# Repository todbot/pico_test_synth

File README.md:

# pico_test_synth

A simple 
[Raspberry Pi Pico RP2040 or Pico 2 RP2350](https://www.raspberrypi.com/documentation/microcontrollers/raspberry-pi-pico.html)-based
synth to experiment with [`synthio`](https://github.com/todbot/circuitpython-synthio-tricks) and [Mozzi](https://github.com/sensorium/Mozzi).

### pico_test_synth2

### pico_test_synth, the original

<h3>video demo</h3>

** **[Available on Tindie](https://www.tindie.com/products/todbot/pico_test_synth/)** **

### Features

* [PCM5102 I2S DAC](https://todbot.com/blog/2023/05/16/cheap-stereo-line-out-i2s-dac-for-circuitpython-arduino-synths/) footprint for high-quality stereo audio out
* Optoisolated MIDI Input via [MIDI TRS-A 3.5mm jack](https://www.perfectcircuit.com/make-noise-0-coast-midi-cable.html)
* MIDI output via MIDI TRS-A 3.5mm jack
* Two pots for controlling parameters
* One switch for controlling parameters
* 16 capsense touch buttons for synth triggering
* USB MIDI in/out of course too
* **(NOTE: the pico_test_synth1 PCB will NOT work with the Pico2, since its RP2350 chip has a hardware error)**

#### pico_test_synth2 vs pico_test_synth

- Both use the same components
- Both run the same code 
- Both fit in the same enclosure
- `pico_test_synth2` drawn in Kicad; `pico_test_synth` drawn in Eagle
- `pico_test_synth2` has square buttons; `pico_test_synth` has round buttons
- `pico_test_synth2` can work with Pico 2 and Pico 
- `pico_test_synth` can only work with Pico1

### Software

Programs written for [`qtpy_synth`](https://github.com/todbot/qtpy_synth/)
will work with this board too with minimal changes.

Some programs written specifically for this board:

* [TBish](https://github.com/todbot/pico_test_synth/tree/main/circuitpython/tbish/) - a TB303-like synth demo ([video demo](https://www.youtube.com/watch?v=1AflpXbEIno))
* [monosynth1](https://github.com/todbot/pico_test_synth/tree/main/arduino/monosynth1) - a full Moog-like monosynth written in Arduino & Mozzi 
* [hwtest](https://github.com/todbot/pico_test_synth/tree/main/circuitpython/hwtest/code.py) - test out the hardware with a simple synth ([video demo](https://www.youtube.com/watch?v=9U2Dn7ckdbs))
* [wavesynth](https://github.com/todbot/pico_test_synth/tree/main/circuitpython/wavesynth/) - port of wavesynth for qtpy_synth board with some improvements

#### See also:
- [CircuitPython Synthio Tricks](https://github.com/todbot/circuitpython-synthio-tricks)
  - Contains [many other synthio examples](https://github.com/todbot/circuitpython-synthio-tricks/tree/main/examples) that can work with this synth with minimal changes
- [Synthio Tutorial](https://todbot.github.io/CircuitPython_Synthio_Tutorial/) 
  - a getting-started guide for `synthio` ending with some full synthesiser voices 

### Enclosure

As seen in the photos, there is a simple [3d-printable enclosure available on Printables](https://www.printables.com/model/784414-case-for-pico_test_synth-circuitpython-synthesizer). 
It's fast to print and you can snap the PCB in to quickly get started,
or use M2.5 screws and nuts to secure the PCB more permanently.

### Pins used

The board uses all of the Raspberry Pi Pico pins:

* `board.GP28` - middle button
* `board.GP27` - right knob
* `board.GP26` - left knob
* `board.GP22` - I2S data
* `board.GP21` - I2S LR  clock
* `board.GP20` - I2S bit clock
* `board.GP19` - I2C SCL for OLED display
* `board.GP18` - I2C SDA for OLED display
* `board.GP17` - TRS UART MIDI in
* `board.GP16` - TRS UART MIDI out
* `board.GP15`..`board.GP0` -- touch pads 1-16

For more details see [`hwtest/code.py`](https://github.com/todbot/pico_test_synth/tree/main/circuitpython/hwtest/code.py).

### Schematics

#### pico_test_synth2 ####

#### pico_test_synth, original ####

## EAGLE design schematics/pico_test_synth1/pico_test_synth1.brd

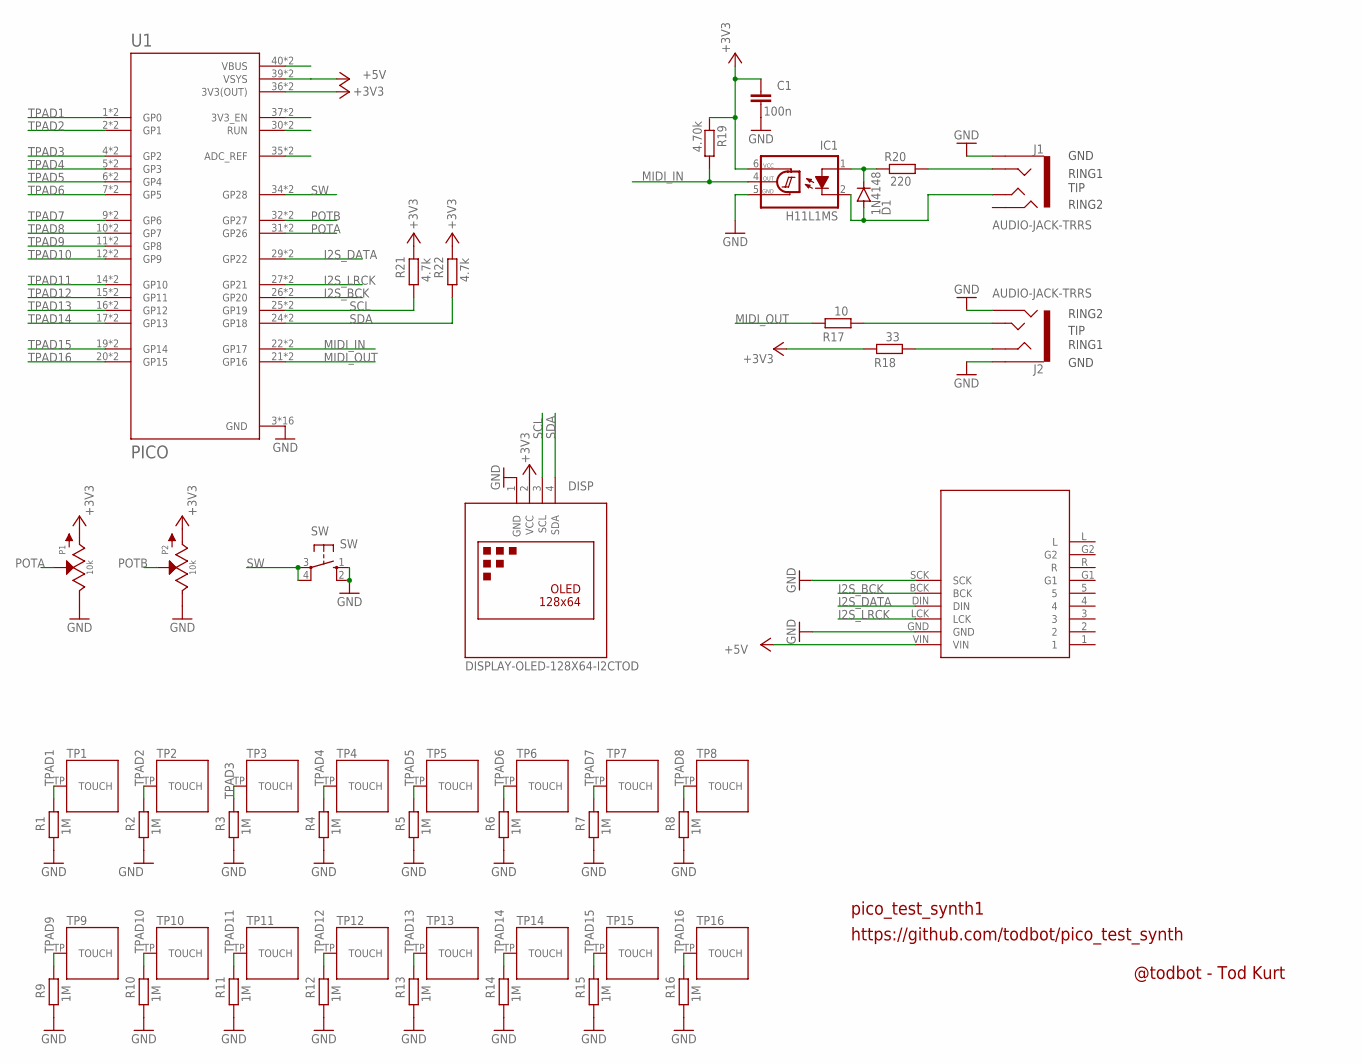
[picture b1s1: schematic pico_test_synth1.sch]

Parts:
C1: 100n; C0805
D1: 1N4148; SOD123
DISP: DISPLAY-OLED-128X64-I2CTOD; DISPLAY-OLED-128X64-I2C-TOD
IC1: H11L1MS; DIL6-SMD; MPN2 H11L1S; LCSC C78589
J1: AUDIO-JACK-TRRS; PJ-320D_SPARKFUN
J2: AUDIO-JACK-TRRS; PJ-320D_SPARKFUN; LCSC C431535
P1, P2: 10k; OG-POTS_ALPS_POT_VERTICAL_WITHBIGKNOB
R1, R2, R3, R4, R5, R6, R7, R8, R9, R10, R11, R12, R13, R14, R15, R16: 1M; R0805
R17: 10; R0805
R18: 33; R0805
R19: 4.70k; R0805
R20: 220; R0805
R21, R22: 4.7k; R0805
SW: SW; B3F-10XX
TP1, TP2, TP3, TP4, TP5, TP6, TP7, TP8, TP9, TP10, TP11, TP12, TP13, TP14, TP15, TP16: TOUCHPADA; TOUCHPADA_0.5IN
U1: PICO; PICO-PKG-NO_DEBUG
U2: I2S_PCM_51XX_SOUNDCARD; I2S_PCM_5100_SOUNDCARD

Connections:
+3V3: C1.1, DISP.2 (VCC), IC1.6 (VCC), P1.P$3 (A), P2.P$3 (A), R18.1, R19.1, R21.1, R22.1, U1.36 (3V3(OUT)), U1.P$36 (3V3(OUT))
+5V: U1.39 (VSYS), U1.P$39 (VSYS), U2.VIN
GND: C1.2, DISP.1 (GND), IC1.5 (GND), J1.EARTH, J2.EARTH, J2.RING2, P1.P$1 (E), P2.P$1 (E), R1.2, R2.2, R3.2, R4.2, R5.2, R6.2, R7.2, R8.2, R9.2, R10.2, R11.2, R12.2, R13.2, R14.2, R15.2, R16.2, SW.1 (S), SW.2 (S1), U1.3 (GND), U1.8 (GND), U1.13 (GND), U1.18 (GND), U1.23 (GND), U1.28 (GND), U1.33 (GND), U1.38 (GND), U1.P$3 (GND), U1.P$8 (GND), U1.P$13 (GND), U1.P$18 (GND), U1.P$23 (GND), U1.P$28 (GND), U1.P$33 (GND), U1.P$38 (GND), U2.GND, U2.SCK
I2S_BCK: U1.26 (GP20), U1.P$26 (GP20), U2.BCK
I2S_DATA: U1.29 (GP22), U1.P$29 (GP22), U2.DIN
I2S_LRCK: U1.27 (GP21), U1.P$27 (GP21), U2.LCK
MIDI_IN: IC1.4 (OUT), R19.2, U1.22 (GP17), U1.P$22 (GP17)
MIDI_OUT: R17.1, U1.21 (GP16), U1.P$21 (GP16)
unnamed: U1.35 (ADC_REF), U1.P$35 (ADC_REF)
unnamed: J1.RING1, R20.2
unnamed: U1.30 (RUN), U1.P$30 (RUN)
unnamed: U1.37 (3V3_EN), U1.P$37 (3V3_EN)
unnamed: U1.40 (VBUS), U1.P$40 (VBUS)
unnamed: D1.C, IC1.1 (A), R20.1
unnamed: D1.A, IC1.2 (C), J1.TIP
unnamed: J2.RING1, R18.2
unnamed: J2.TIP, R17.2
POTA: P1.P$2 (S), U1.31 (GP26), U1.P$31 (GP26)
POTB: P2.P$2 (S), U1.32 (GP27), U1.P$32 (GP27)
SCL: DISP.3 (SCL), R21.2, U1.25 (GP19), U1.P$25 (GP19)
SDA: DISP.4 (SDA), R22.2, U1.24 (GP18), U1.P$24 (GP18)
SW: SW.3, SW.4 (P1), U1.34 (GP28), U1.P$34 (GP28)
TPAD1: R1.1, TP1.TP, U1.1 (GP0), U1.P$1 (GP0)
TPAD2: R2.1, TP2.TP, U1.2 (GP1), U1.P$2 (GP1)
TPAD3: R3.1, TP3.TP, U1.4 (GP2), U1.P$4 (GP2)
TPAD4: R4.1, TP4.TP, U1.5 (GP3), U1.P$5 (GP3)
TPAD5: R5.1, TP5.TP, U1.6 (GP4), U1.P$6 (GP4)
TPAD6: R6.1, TP6.TP, U1.7 (GP5), U1.P$7 (GP5)
TPAD7: R7.1, TP7.TP, U1.9 (GP6), U1.P$9 (GP6)
TPAD8: R8.1, TP8.TP, U1.10 (GP7), U1.P$10 (GP7)
TPAD9: R9.1, TP9.TP, U1.11 (GP8), U1.P$11 (GP8)
TPAD10: R10.1, TP10.TP, U1.12 (GP9), U1.P$12 (GP9)
TPAD11: R11.1, TP11.TP, U1.14 (GP10), U1.P$14 (GP10)
TPAD12: R12.1, TP12.TP, U1.15 (GP11), U1.P$15 (GP11)
TPAD13: R13.1, TP13.TP, U1.16 (GP12), U1.P$16 (GP12)
TPAD14: R14.1, TP14.TP, U1.17 (GP13), U1.P$17 (GP13)
TPAD15: R15.1, TP15.TP, U1.19 (GP14), U1.P$19 (GP14)
TPAD16: R16.1, TP16.TP, U1.20 (GP15), U1.P$20 (GP15)

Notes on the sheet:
pico_test_synth1
https://github.com/todbot/pico_test_synth
RING2
RING1
GND
TIP
@todbot - Tod Kurt

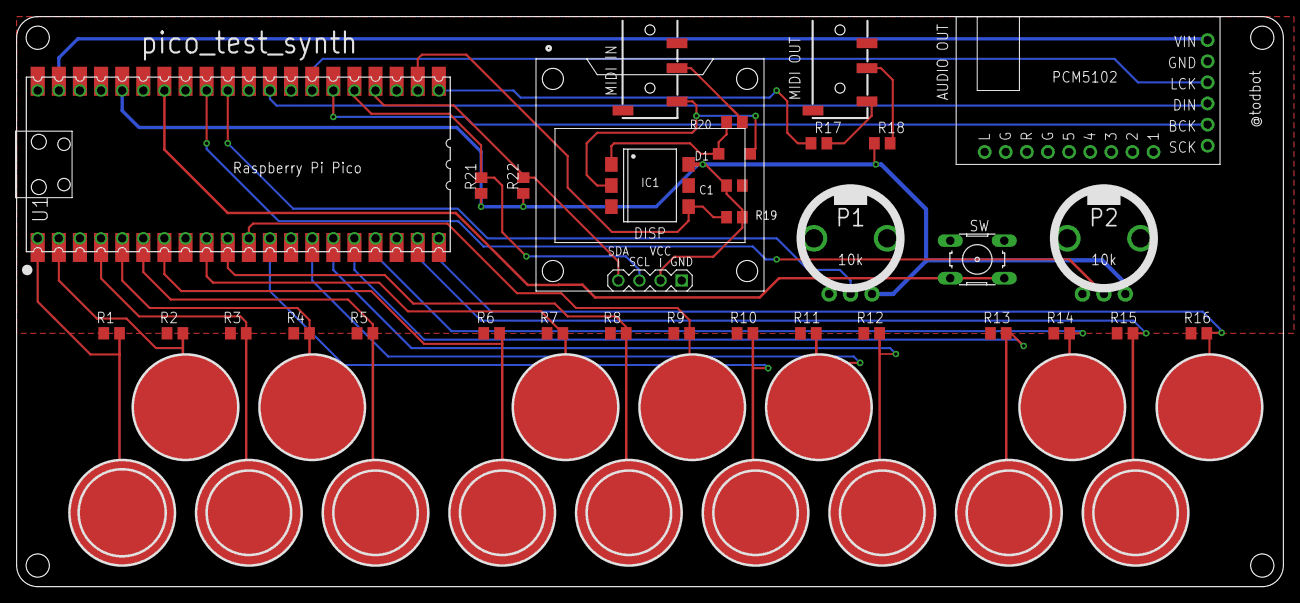
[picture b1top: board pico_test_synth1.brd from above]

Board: 2 copper layers, 152.4 x 68.6 mm, 49 parts (0 on the bottom side), 38 nets.

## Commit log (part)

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2023-08-08 first
2023-08-18 fix up pin usage typos, addresses issue #1
2023-11-22 add synth w/ basic hardware abstraction
2023-11-22 typo fix
2023-11-23 synth1
2024-02-16 clean up hwtest, add rudimentary MIDI receive
2024-02-16 cleanup hwtest a little
2024-02-16 first cut at port of wavesynth from qtpy_synth
2024-02-16 cleanup wavesynth app
2024-02-17 add octave and volume to synthio_instrument patches, expose those params in wavesynth, misc cleanups and fixes. still hate pickup mode
2024-02-17 mention wavesynth in readme
2024-02-17 wavesynth install notes
2024-02-26 finally checking in the restructuring
2024-02-27 add case link to README
2024-02-27 fix wavesynth bugs
2024-02-28 fix more new wavesynth bugs
2024-02-28 wavesynth fixup
2024-02-29 more wavesynth fixes
2024-02-29 wavesynth back to async
2024-03-01 wavesynth filter env works more like it should now
2024-03-01 add some docs
2024-03-02 progress on patch save/load
2024-03-02 wavesynth: patch save/load sorta works, added patch name to display, reworked wave_select logic, added noise wave_select
2024-03-03 wavesynth gauges now redraw on patch selection
2024-03-03 wavesynth twiddling
2024-03-03 wavesynth add splashscreen
2024-03-03 wavesynth instrument.py cleanup
2024-03-03 small hwtest amp env change
2024-03-04 make all waves be half-amplitude (16833) for better multi-voice summing, split out load/save UI actions a little
2024-03-04 wavesynth: add basic velocity sensitivity
2024-03-04 wavesynth: need boot.py to save patches
2024-03-04 fix exec bit on patch_saver.py
2024-03-05 wavesynth: cleanup and added start of demo patch bank
2024-03-28 fix video demo link in readme
2024-07-04 finally getting some arduino examples
2024-07-06 working on arduino gui
2024-07-18 small updates
2024-07-28 add touch keys to monosynth1
2024-07-28 monosynth1: add serial midi in, add start of display
2025-02-15 route +5V to PCM5102 module instead of +3V3, fixes #2
2025-04-15 redraw board in kicad, add ability for using pico2 rp2350
2025-04-16 fixes
2025-04-18 pcb2 cleanup before production
2025-04-18 move pico_test_synth1 sch
2025-04-25 finally check in captouch-only hwtest
2025-04-28 update hwtest for modern circuitpython
2025-05-03 fix up hwtest/code.py a little
2025-05-05 pico_test_synth2 updates
2025-05-15 add pico_test_synth2 to readme
2025-05-15 adj img widths
2025-05-15 add pico_test_synth2 vs original differences
2025-05-25 finally checking in TB-like synth
2025-05-25 finally checked in
2025-05-26 tbish now has touchpad control
2025-05-26 tbish tuning
2025-05-26 tbish slide sorta working
2025-05-27 tbish: misc fixes, added delay (but off)
2025-05-27 tbish envmod and decay work a bit more like 303 now
2025-05-28 tbish: pulled out simple step sequencer to its own class, modeled after synth_tools.step_sequencer
2025-05-29 hooked up delay to knobs, added first cut at save/load of ParamSets
2025-05-29 added wavetype to UI, changed around some other UI, restored drive_mix
2025-05-31 tbish: wired up accent param better, tweaked distortion, added saw2 wave
2025-06-01 tbish: better accent, step display
2025-06-03 add quick tbish readme
2025-06-05 pico_test_synth2 5Jun2025 production run
2025-06-09 fix spdx on .py
2025-06-09 clarify pico2 in readme
2025-06-09 update demos in readme
2025-06-09 update links in readme
2025-11-28 update hwtest/code.py to work with pico_test_synth2 board
2025-11-29 cleanup hwtest code
2025-12-02 fix synth1 for cirpy 10 and pico_test_synth2
2025-12-02 add filter type selection to synth1
2025-12-03 make synth1 dual-voice with detune
2025-12-04 synth1: add simple filter envelope
2025-12-05 synth1 now has per-note filter env with adjustable filter env time using exp filter instead of linear
2025-12-05 synth1: add osc and detune
2025-12-05 synth1: add proper midi input
2025-12-07 cleanup synth1
2025-12-08 synth1: rename pico_test_synth.py to pico_test_synth_hardware.py
2025-12-08 wavesynth1 fixes
2025-12-08 update gitignore
2025-12-08 change synth_tools/instrument to change filter type on keypress
2026-01-14 add video demo link
